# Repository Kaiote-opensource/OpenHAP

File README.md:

# OpenHAP
A low cost, opensource research tool with remote measurement capability for non invasive, stationary monitoring of household air pollution.

---

General parameters monitored include: 

* **Household air pollution** using either PM 1/2.5/10 as pollution indicators.

* **Stove temperatures** in order to attribute pollution measurements above to stove characteristics while in use to answer questions such as - What phase of stove use is pollution highest for a given stove type?

* **Associated human behavioral patterns.** This is to infer behaviour that may have an indirect contribution to pollution. The device infers this by processing wireless beacons emitted by bluetooth wrist straps worn by the members of the household under study. This allows monitoring behaviour and exposure of upto 20 individuals in the same household.

OpenHAP is designed as a modular software/firmware layer that supports customizable measurement hardware. It utilises open datalogging file formats such as:

* **.csv** for timestamped measurement data.

Figure: Sample 2D thermal image(32x24 pixels) of a human being during testing. Temperature is shown on the Z axis on the GIF. Thermal images are used to correlate stove temperature to Particulate measurements. Stove temperature can be well inferred from our tests if the stove is within the sensor's field of view. See graphical plots below from two households chosen from Kibera and rural Kenya(Kiambu).

# Sample results

Measurement results for a rural low income household,Kiambu Kenya with two middle aged women. Household energy use - Three Stone Open Fire(TSOF)

Measurement results for an urban low income household,Kibera Kenya occupied by a man, wife and 2 children. Children were not monitored in our study as majority of their time was spent with the mother. Household energy use - Kerosene and charcoal briquettes.

# Documentation
OpenHAP's story is covered in [this hackaday article](https://hackaday.com/2019/09/24/fighting-household-air-pollution/) with indepth technical documentation at [this link](https://hackaday.io/project/166510-openhap)

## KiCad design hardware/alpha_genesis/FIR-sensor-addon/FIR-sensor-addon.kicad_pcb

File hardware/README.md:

# Hardware versions

* **alpha_genesis** - Initial hardware version

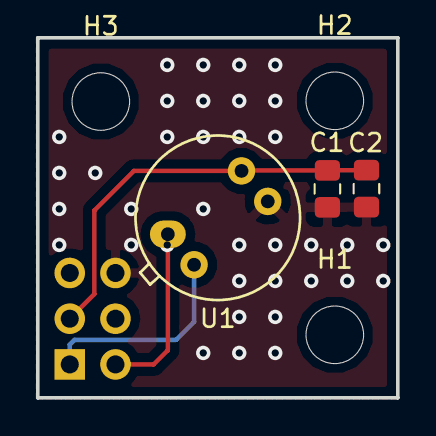
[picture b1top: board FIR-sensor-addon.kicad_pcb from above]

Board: 2 copper layers, 20.0 x 20.0 mm, 7 parts (1 on the bottom side), 4 nets.

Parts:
C1: 0.1uF/25V(10%)/0805; C_0805_2012Metric_Pad1.15x1.40mm_HandSolder
C2: 1uF/6.3v(10%)/0805; C_0805_2012Metric_Pad1.15x1.40mm_HandSolder
H1, H2, H3: MountingHole; MountingHole_3.2mm_M3
J1: Conn_02x03_Odd_Even; PinHeader_2x03_P2.54mm_Vertical
U1: MLX90640

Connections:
+3V3: C1.1, C2.1, J1.3, U1.2
/SCL: J1.1, U1.4
/SDA: J1.2, U1.1
GNDREF: C1.2, C2.2, J1.6, U1.3

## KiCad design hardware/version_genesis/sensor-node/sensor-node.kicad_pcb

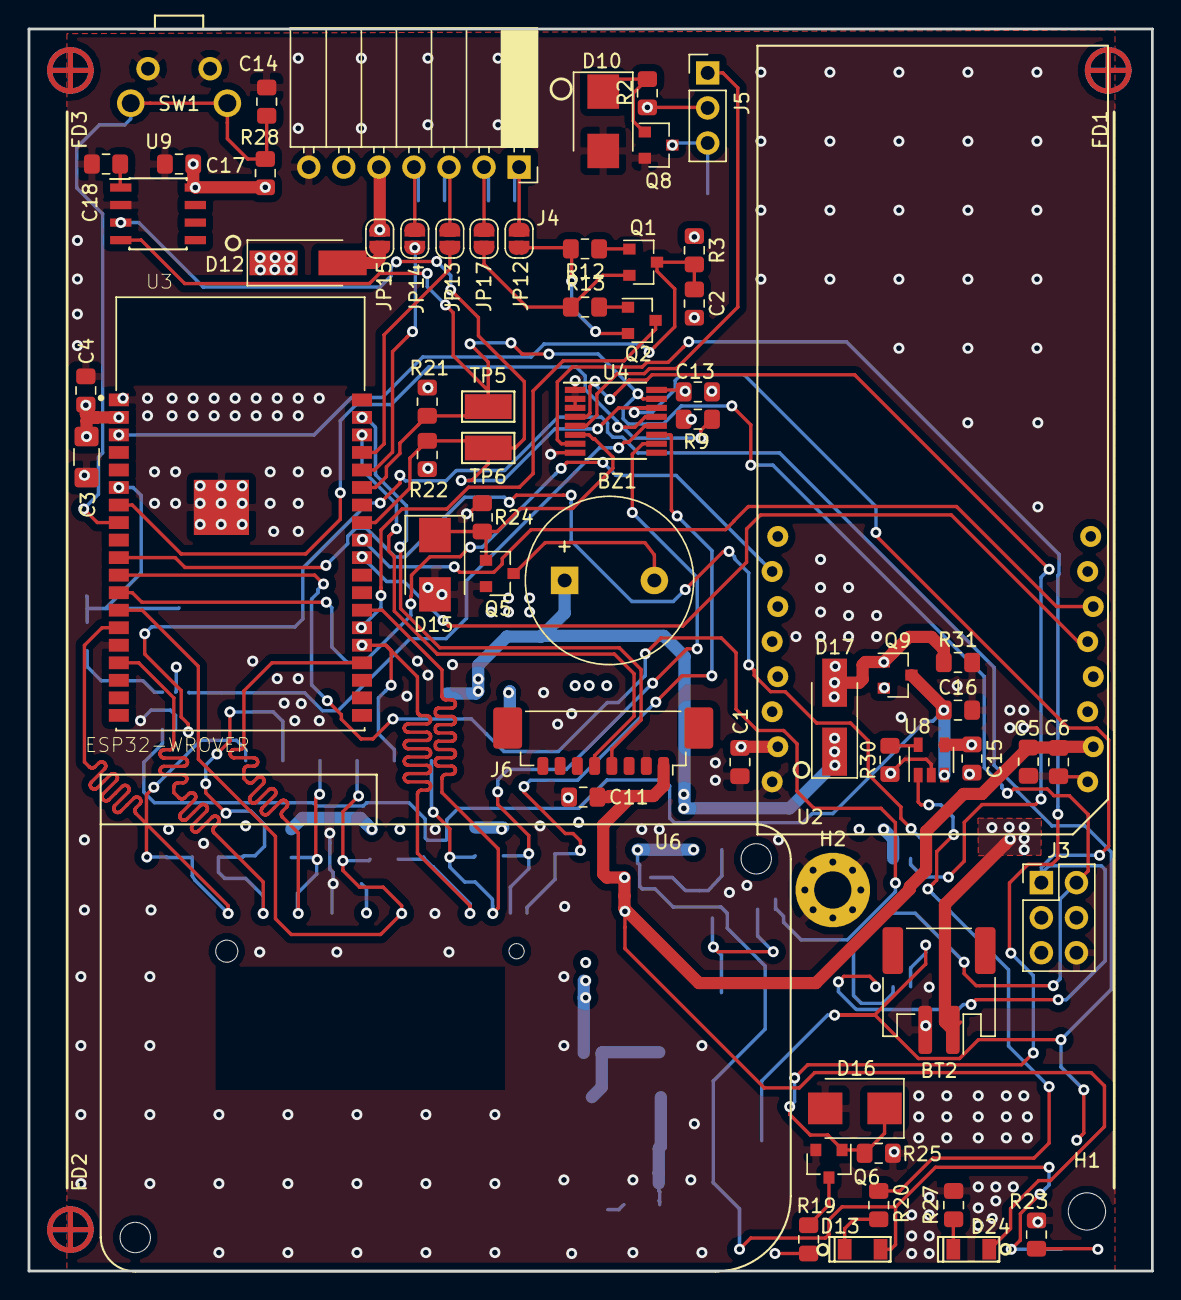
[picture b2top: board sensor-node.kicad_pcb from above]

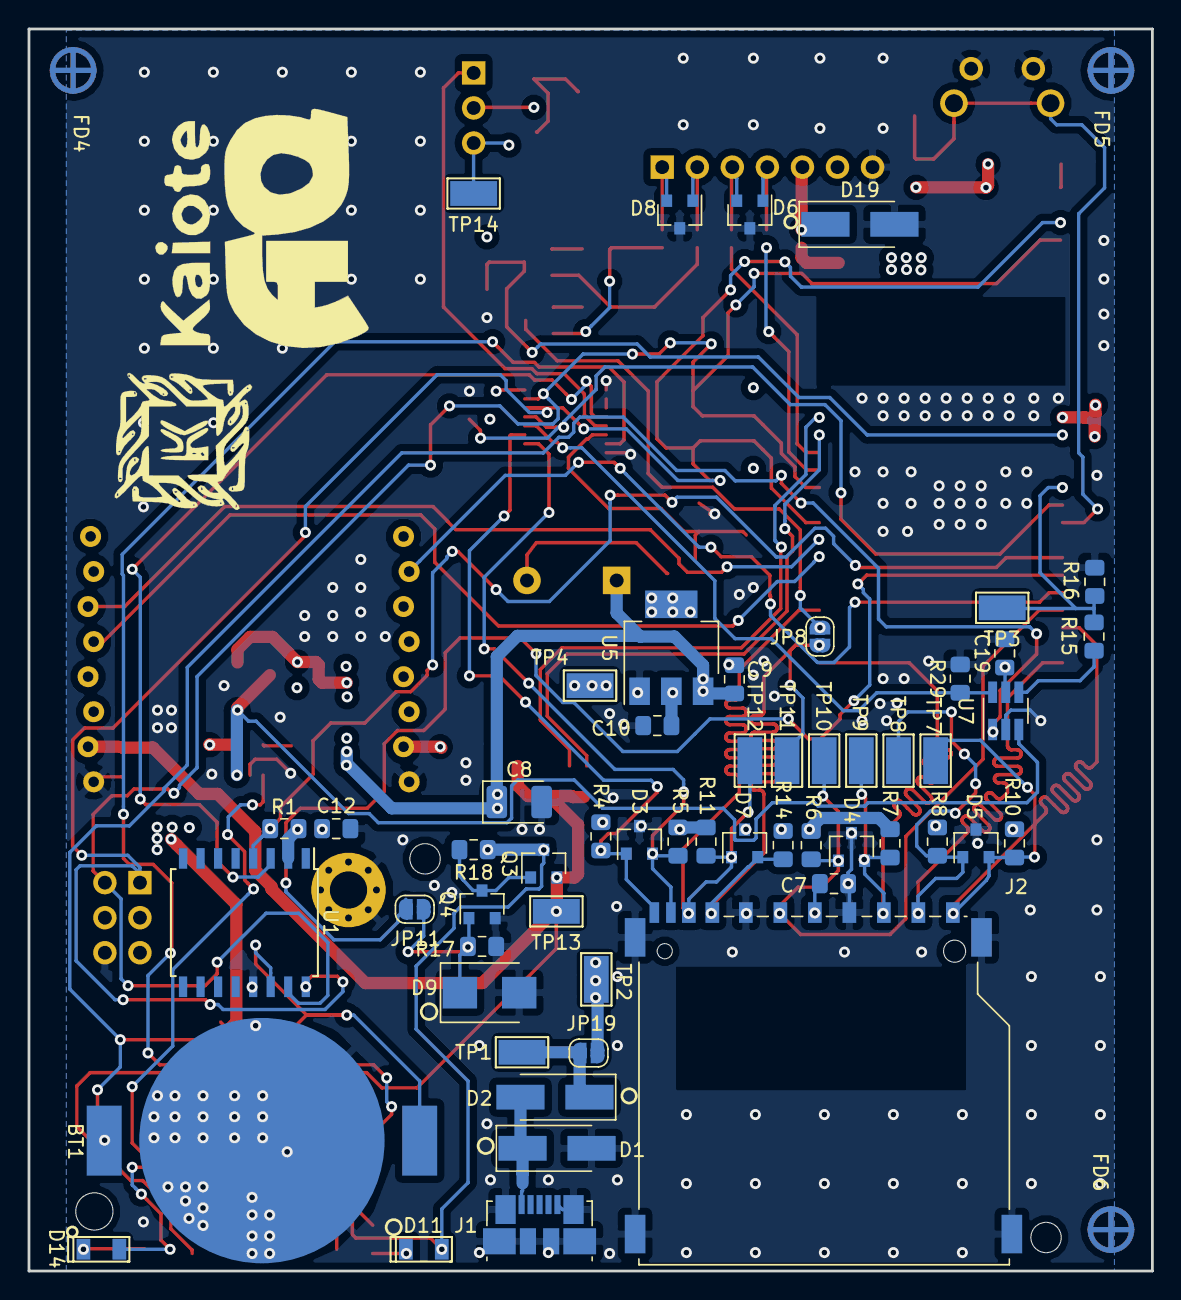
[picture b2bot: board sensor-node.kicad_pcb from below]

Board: 4 copper layers, 81.4 x 90.0 mm, 127 parts (60 on the bottom side), 62 nets.

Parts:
BT1: Battery_Cell; BAT-HLD-001-xx-OTL
BT2: Battery_Cell; JST_PH_S2B-PH-SM4-TB_1x02-1MP_P2.00mm_Horizontal
BZ1: Buzzer; Buzzer_12x9.5RM6.5
C1, C5, C11, C12, C13, C18, C19: 0.1uF/25V(10%)/0805; C_0805_2012Metric_Pad1.15x1.40mm_HandSolder
C2, C14: 1nF/50v(10%)/0805; C_0805_2012Metric_Pad1.15x1.40mm_HandSolder
C3: 100uF/6.3v(20%)/1206; C_1206_3216Metric_Pad1.42x1.75mm_HandSolder
C4: 1uF/6.3v(10%)/0805; C_0805_2012Metric_Pad1.15x1.40mm_HandSolder
C6, C7, C9, C10: 10uF/25V(10%)/0805; C_0805_2012Metric_Pad1.15x1.40mm_HandSolder
C8: 220uF/tantalum; CP_EIA-3528-15_AVX-H_Pad1.50x2.35mm_HandSolder
C15, C16: 4.7uF/16v/10%/0805; C_0805_2012Metric_Pad1.15x1.40mm_HandSolder
C17: 220nF/50V(10%)/0805; C_0805_2012Metric_Pad1.15x1.40mm_HandSolder
D1, D19: TVS_5V; D_SMA_Handsoldering
D2, D12, D17: D_Schottky; D_SMA_Handsoldering
D3, D4, D5, D6, D7, D8: CDSOT23-T03C; SOT-23
D9, D10, D15, D16: TVS_3V3; D_SMB
D11: Red/RA; APA2106SRCPRV
D13, D14, D24: Green/RA; APA2106SRCPRV
FD1, FD2, FD3, FD4, FD5, FD6: Fiducial; Fiducial_classic_Small_CopperBottom_Type1
H1: MountingHole; MountingHole_2.7mm_M2.5
H2: MountingHole_Pad; MountingHole_2.7mm_M2.5_Pad_Via
J1: USB_B_Micro; USB_Micro-B_Molex_47346-0001
J2: TE_2041021; SD_TE_2041021
J3: Conn_02x03_Odd_Even; PinHeader_2x03_P2.54mm_Vertical
J4: Conn_01x07; PinSocket_1x07_P2.54mm_Horizontal
J5: Conn_01x03_Male; PinHeader_1x03_P2.54mm_Vertical
J6: Conn_01x08; Molex_PicoBlade_53398-0871_1x08-1MP_P1.25mm_Vertical
JP8, JP11, JP12, JP13, JP14, JP15, JP17, JP19: SolderJumper_2_Open; SolderJumper-2_P1.3mm_Open_RoundedPad1.0x1.5mm
LOGO1: kaiote_logo; pcb-logo
LOGO2: AQ_logo; AQ
Q1, Q2: S8050; SOT-23
Q3, Q9: SI2323DDS-T1-GE3; SOT-23
Q4, Q5, Q6, Q8: BSS138; SOT-23
R1, R2, R3, R4, R5, R6, R7, R8, R9, R10, R11, R14, R17, R24, R25, R28: 10k(5%); R_0805_2012Metric_Pad1.15x1.40mm_HandSolder
R12, R13: 12k(1%); R_0805_2012Metric_Pad1.15x1.40mm_HandSolder
R15, R16, R29: 10k(0.5%); R_0805_2012Metric_Pad1.15x1.40mm_HandSolder
R18, R31: 100k(5%); R_0805_2012Metric_Pad1.15x1.40mm_HandSolder
R19, R20: 470R(5%); R_0805_2012Metric_Pad1.15x1.40mm_HandSolder
R21, R22: 2.4k(5%); R_0805_2012Metric_Pad1.15x1.40mm_HandSolder
R23, R27: 2K(5%); R_0805_2012Metric_Pad1.15x1.40mm_HandSolder
R30: 2.4k(0.1%); R_0805_2012Metric_Pad1.15x1.40mm_HandSolder
SW1: E-switch TL1105VF160Q
TP1, TP2, TP3, TP4, TP5, TP6, TP7, TP8, TP9, TP10, TP11, TP12, TP13, TP14: TestPoint_Keystone_5015_Micro-Minature
U1: DS3231SN; SOIC-16W_7.5x10.3mm_P1.27mm
U2: MIKROE_CLICK_GSM; MIKROE_CLICK
U3: ESP32-WROVER; XCVR_ESP32-WROVER-I
U4: TCA9534; TSSOP-16_4.4x5mm_P0.65mm
U5: NCP1117-3.3_SOT223; SOT-223-3_TabPin2
U6: ZH03; KAIOTE_ZH03B
U7: 74LVC1G3157; SOT-23-6_Handsoldering
U8: MCP73812T-420I-OT; SOT-23-5
U9: HIH6030-021-001; SOIC-8_3.9x4.9mm_P1.27mm

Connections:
+3V3: C1.1, C3.1, C4.1, C7.1, C10.1, C12.1, C13.1, C17.2, C19.1, J2.4, J3.3, J5.2, R1.1, R2.2, R3.1, R4.1, R5.1, R6.1, R7.1, R8.1, R9.1, R10.1, R11.1, R14.1, R21.1, R22.1, R28.1, TP4.1, U1.2, U2.7, U3.2, U4.16, U5.2, U7.5, U9.8
+5V: C15.1, D12.1, D17.2, JP19.2, Q9.1, R31.1, TP2.1, U8.4
/5V_I: D19.1, J4.5, JP15.2
/BATT_SEL: R29.1, U4.12, U7.6
/BATT_SENSE: R15.2, R16.1, TP3.1, U3.6
/CD: D3.1, J2.11, R4.2, U4.11
/CELL_RX: U2.12, U3.29
/CELL_TX: U2.11, U3.30
/CHARGE: R20.2, U8.1
/CLK: D4.1, J2.5, R6.2, TP10.1, U3.13
/CMD: D4.2, J2.2, R7.2, TP9.1, U3.23
/DATA0: D7.2, J2.7, JP8.1, R14.2, TP11.1, U3.24
/DATA1: D7.1, J2.8, R11.2, TP12.1, U3.26
/DATA2: D5.2, J2.9, R10.2, TP7.1, U3.14
/DATA3: D5.1, J2.1, R8.2, TP8.1, U3.16
/DTR: JP12.1, Q2.2, R12.2
/DTR-I: D8.2, J4.1, JP12.2
/EN: C2.1, Q1.3, R3.2, U3.3
/IO0: JP8.2, Q2.3, U3.25
/LOAD: C5.1, C6.1, C11.1, D24.2, J6.1, Q3.2, TP13.1, U2.15
/LOAD_CTRL: JP11.1, U3.11
/O_BUZZER: D15.1, Q5.1, R24.1, U4.6
/O_WARN: D16.1, Q6.1, R25.1, U4.7
/PIR_INTERRUPT: J5.1, U4.5
/PIR_RETURN: J5.3, Q8.3, TP14.1
/PWR_KEY: U2.2, U3.12
/RTC_INTERRUPT: U1.3, U4.4
/RTS: JP17.1, Q1.2, R13.2
/RTS_I: D8.1, J4.2, JP17.2
/RXD: JP13.1, U3.35
/RXD-I: D6.2, J4.3, JP13.2
/RXD_PM2.5: J6.4, U3.37
/SCL: J3.1, R22.2, TP6.1, U1.16, U3.31, U4.14, U9.3
/SDA: J3.2, R21.2, TP5.1, U1.15, U3.33, U4.15, U9.4
/TXD: JP14.1, U3.34
/TXD-I: D6.1, J4.4, JP14.2
/TXD_PM2.5: J6.5, U3.36
/VBATT: BT1.1, U1.14, U7.1
/VBATT_PWR: BT2.1, C16.1, Q9.3, U7.3, U8.3
/WARN_LED: Q6.3, R19.2
/WP: D3.2, J2.10, R5.2, U4.10
/~FACTORY_RST: C14.1, R28.2, SW1.1, U3.8
/~I_INTERRUPT: R9.2, U3.7, U4.13
/~O_RTC_RST: R1.2, U1.4, U3.10
/~PIR_RST: D10.1, Q8.1, R2.1
GND: BT1.2, BT2.2, C1.2, C2.2, C3.2, C4.2, C5.2, C6.2, C7.2, C8.2, C9.2, C10.2, C11.2, C12.2, C13.2, C14.2, C15.2, C16.2, C17.1, C18.1, C19.2, D1.2, D3.3, D4.3, D5.3, D6.3, D7.3, D8.3, D9.2, D10.2, D15.2, D16.2, D19.2, H2.1, J1.5, J1.6, J2.3, J2.6, J2.12, J3.6, J4.7, J6.2, Q4.2, Q5.2, Q6.2, Q8.2, R16.2, R17.1, R23.2, R24.2, R25.2, R27.2, R29.2, R30.2, R31.2, SW1.2, U1.13, U2.8, U2.16, U3.1, U3.15, U3.38, U3.39, U4.1, U4.2, U4.3, U4.8, U5.1, U7.2, U8.2, U9.2
unnamed: BZ1.2, Q5.3
unnamed: C18.2, U9.1
unnamed: D1.1, D2.2, J1.1
unnamed: D2.1, JP19.1, TP1.1
unnamed: D9.1, JP11.2, Q4.1, R17.2
unnamed: D11.1, R19.1
unnamed: D12.2, JP15.1
unnamed: D13.1, R20.1
unnamed: D14.1, R23.1
unnamed: D24.1, R27.1
unnamed: Q1.1, R12.1
unnamed: Q2.1, R13.1
unnamed: Q3.1, Q4.3, R18.2
unnamed: R15.1, U7.4
unnamed: R30.1, U8.5
VDD: BZ1.1, C8.1, C9.1, D11.2, D13.2, D14.2, D17.1, Q3.3, Q9.2, R18.1, U5.3

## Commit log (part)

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2019-03-11 Add firmware and hardware design files
2019-03-11 Change BLE component name and update README
2019-03-11 Captive portal intial update
2019-03-11 Add libesphttpd submodule
2019-03-12 interface design update
2019-03-19 socket modification update
2019-03-19 div assignment update
2019-03-19 minor change
2019-03-19 minor change update
2019-03-19 vendor ignore
2019-03-19 vendo rename to resources
2019-03-19 testing update
2019-03-19 infrared page minor changes
2019-03-19 integer update
2019-03-21 graph update
2019-03-22 ui update
2019-04-02 UI updates
2019-04-04 interface update
2019-04-04 unix time update
2019-04-05 change request update
2019-04-05 change update
2019-04-08 dynamic update
2019-04-08 url update
2019-04-09 heatmap refinement
2019-04-09 segmented byte array update
2019-04-12 IMAGE ASPECT RATION UPDATE
2019-04-12 tag page implementation
2019-04-13 Add untracked files
2019-04-13 Bugfix: Eliminate duplicate i2c bus mutexes
    Removed bug where each device on the bus had its own bus mutex. This led to a situation whereby the bus could be accessed at the same time leading to undefined behaviour.
2019-04-13 Code refactoring:
2019-04-13 Fix main source file formatting
2019-04-17 tag page beep update
2019-04-18 message received audio update
2019-04-18 true update
2019-04-18 tag time update
2019-04-19 Add Task notifications
    1. Added task notifications to allow tasks to exit cleanly when there are no clients on a page. The task is notified via an event group, deallocates its structures and deletes itself.
    2. Incorporated the ZH03 sensor and implemented a 5 element ring buffer queue between particulate matter sensor handler task and the status task.
    3. Used fix (1) above in this commit to fix bug that would show up when the client clicked on a separate tab when moving from the index page and went back. The particulate matter sensor would not wor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
2019-04-19 Display zeroed image on infared failure
    1. Added feature to display zero filled image buffer in the event of error during thermal buffer fetch from sensor.
2019-04-19 Add ws burst string broadcast function
    1. Refactored code to add utlity function for burst broadcasts of base64 encoded binary data, whose base64 length exceeds HTTPD's send buffer limit. Currently this limit is currently 2kB. The functio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
2019-04-19 Remove references to pdPass
    1. Removed references to pdPass as pdPass is equivaluent to true or (1), making its equivalence check redundant within an if statement.
2019-04-19 Add firmware folder .gitignore file
    1. Removed build folder and any lock files at firmware top level directory generated by libreoffice when editing the partitions csv file.
    2. Add .gitignore with reference to (1) above.
2019-04-19 Change Wifi/BLE preferences
    1. Changed preferences in sdkconfig to give more priority to BLE with regard to shared antenna air time.
2019-04-19 updating libesphttpd to latest
2019-04-19 Add espfs as component
2019-04-19 Reflect upstream changes
2019-04-20 Setup ble tag info page
    1. Setup BLE tag info page to optimal settings. Now BLE TLM packets can be received well.
    2. There is still a bug when moving from the tag info page and back as the ble hardware never returns scanning results.
2019-04-23 Changed task closing sequencing on close event
    1. As we depend on the PM 2.5 values passed by value from the PM sensor handler, and its ambiguity due to the ampersand sign, we would like to complete dereferecing its reference first(If that is its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
    2. This is talked about by the comment " FreeRTOS queue will ALWAYS use copy-by-value, as that is how the queue operation is defined, the only question becomes what is the 'value' to be copied, is it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
2019-04-24 storage update
2019-04-24 test update
2019-04-24 update 3
2019-04-24 proximity update
2019-04-24 Remove async tasks nd events
    1. Removed async tasks and events such as UART and GPIO event from the I2C GPIO expander.
    2. Added features to ZH03 HAL such as QA mode, low power dormant mode.
2019-04-25 Add acquisition task
    1. Added acquisition task in readiness for field tests. Set task stack size as 16kB.
    2. Added a method to cleanly close the webserver via event groups with feedback to the calling task.
    3. Fixed BLE bug in the webserver page, that affected proximity readings and mesage pings.
2019-04-26 Move power profiling files
2019-04-26 Reworked acquisition task
    1. Added statistics header file that shall hold algorithms to use.
    2. Reworked tasks such as the webserver task that was straining the wifi task by increasing its blocking time from 100ms to 1000ms, as the webserver task had priority 10 while wifi had 23, of which t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
    3. Other additions.
2019-04-27 Add fielded firmware
    1. Add bluetooth and tag info recording functionality during data acquisition.
    2. Add current consumption profile for this specific firmware.
2019-05-12 Add floating point value checks
    1. Added parameter exitInfNan to control ignoring Nan and inf values, if true, the function exits on the first inf or Nan value, if false, the function ignores such values.
    2. Added parameter computeSize to indicate the number of elements the function as computed on if it has successfully exited, this value is less any inf or Nan values in the input array if exitInfNan 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
2019-05-12 Add const qualifier to stats functions prototype parameters
    1. Added const as an extra layer of compile time checks against modifying values in the statistical functions.
2019-05-16 Add C2numpy component
    1. Add C2numpy component in order to save thermal images to a single npy/npz file for field post analysis.
2019-05-22 range update
2019-05-25 Minor changes
2019-08-26 Captive portal Interface restructure
2019-09-14 Add MLX90640 Python scripts folder
    1. Added python scripts folder to allow testing of the MLX90640. As at now the scripts plot temperature for a static thermal image but dynamically streamed images will be added.
2019-09-14 Removed array size check for less than zero 1. Removd check for array size parameter passed because size_t variable is always guaranteed to be unsigned according to the C standard. More documentation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
2019-10-12 Rename DS3231 component folder to external_i2c_rtc
    1. Add max value for all enums to force compiler to keep size under 1 byte during compilation.
    2. Highlight work done on ds3231_set_time() and ds3231_get_time() in line with ESP32 nuance with SNTP vs UNIX time.
    3. Modified ds3231_set_alarm() to allow setting both alarms together in a single function call as opposed to the mutually exclusive implementation (Alarm 1 or Alarm 2) as was implemented prior.
    4. Removed repetitive calls to xSemaphoreTake() and xSemaphoreGive(), implementing this only on the lowest layer that interacted with I2C hardware.
    5. Initialise all local variables.
    6. Added sanity checks on function inputs for parameter valid
2019-10-12 Add ds3231 i2c timeout
    1. Renamed source and header files to lower case.
    2. Minor formatting changes.
    3. Added i2c timeout and log tag as a const variable to allow the linker to set this in the .rodata section of the bin file.
2019-10-13 Easier folder and src/hdr file naming scheme
    1. Changed folder naming scheme to the general device class name without including any of its characteristics, for example, i2c or uart.
    2. Changed the source and header file name of the specific device to include its characteristics that affect hardware, for example, communication protocol used, which would thus affect pin usage in h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
2019-10-13 Apply data hiding
2019-10-13 Add LICENSE details
2019-10-13 Rename particulate matter sensor folder
2019-10-14 Commit with minor additions on PM sensor
2019-10-16 Additional changes to PM sensor code
2019-10-16 Minor corrections and additions to PM sensor codebase
2019-10-18 Finalise particulate matter sensor src code
2019-10-18 Finalise particulate matter sensor src and hdrcode
2019-10-18 Minor renaming
2019-10-18 Checksum calculation changes
2019-10-19 Add additional driver folders by rename
2019-10-19 Add correct renaming scheme
2019-10-20 Modify onchip ADC driver
    1. Modified the onchip ADC driver to take in ADC channel, sample width and attenuation parameters from user code instead of being set statically internally.
    2. Added error checking
    3. Added ADC struct declaration in onchip_adc.h header file
2019-10-20 Add function tca9534_get_port_direction()
    1. Added the above function in order to refactor tca9534_get_pin_direction to avoid code duplication.
    2. Renamed header guard in i2c_tca9534a.h header file
    3. Cleaned up user code definitions in i2c_tca9534a.h header file
2019-10-20 Push header guard changes mentioned earlier
2019-10-20 Change variable type name defining pin directions 1. Changed 'tca9534a_pintype_t' enum type to tca9534a_pin_direction_t 2. Removed pin polarity enum as polarity is not supported by default.
2019-10-20 Removed spacings in uart_zh03.h header file
2019-10-20 Add all changes in firmware folder
2019-10-20 Moved firmware folder to repo root
2019-10-20 Update submodules
2019-10-20 modify gitmodules after folder movement
2019-10-20 Add 2 sample OpenHAP data captures
2019-10-20 Rename data samples folder
2019-10-20 Remove old data filename from repo
2019-10-20 Add assets folder
2019-10-20 Correct year of datafile capture from 2018 to 2019
2019-10-20 Add hackaday article to readme
2019-10-21 Try center aligned list in readme
2019-10-21 Try center aligned list again in readme
2019-10-21 Try normal markdown formatting
2019-10-21 Add OpenHAP video to readme
2019-10-21 Correct typo
2019-10-21 Add hackaday.io image link
2019-10-21 Move hardware associated files
2019-10-21 Add empty readme file
2019-10-21 Add sample results to readme
2019-10-21 Make corrections to readme
2019-10-21 Add details to storage formats in readme
2019-10-21 Add Thermal image details
2019-10-21 Remove thermal image details
2019-10-21 Clean up Honeywell hih6030 driver code
2019-10-21 Update readme formatting
2019-10-21 Add datasheets and technical reference manuals(TRMs)
    Datasheets subfolders shall follow the same layout as the drivers subfolders within the firmware components folder.
2019-10-21 Add README and rename datasheets folder
2019-10-21 Try side by side images
2019-10-21 Change README formatting
2019-10-21 Add locally labelled OpenHAP image
2019-10-21 Added check for negative value rxbytes
2019-10-21 Add MIT license file
2019-10-21 Rename license file
2019-10-22 Remove jupyter notebook saved checkpoints folder
2019-10-22 Add research papers folder
2019-10-22 Change hardware version naming
2019-10-22 Add content to README in docs folder
2019-10-22 Add Bolden folder names in hardware folder README
2019-10-22 Add details to the Firmware folder's README
2019-10-22 Correct misformatted image
2019-10-22 Minor corrections on README
2019-10-22 Changed OpenHAP labelled image
2019-10-22 Add rural Kenya results
2019-10-22 Correct image names
2019-10-22 Add README in samples folder
2019-10-23 Rename samples folder for clarity
2019-10-23 Minor rename
2019-10-23 Update README with bluetooth fields info
    Added Bluetooth tag ID_mean_dBm and Bluetooth tag ID_count description
2019-10-23 Correct information in README
    Updated time field description
2019-10-23 Add temperature snapshot data
2019-10-23 Eliminate unnecessary spacing
2019-10-23 Add other notifier badges
2019-10-23 Eliminate spacing
2019-10-24 Partial reformatting of code layout
    Reformatted code layout for esp_eddystone_api.c
2019-10-26 Cropped power consumption graph
2019-10-26 Changed title in README
2019-11-07 Add citations to research papers folder
2019-11-09 Add license and description to cnumpy
2019-11-09 Fix errors in README
2020-06-10 Update documentation with relevant information
2020-06-10 Add background details
2020-06-10 Update information on bluetooth processing
2020-06-10 Update info on maximum limits
